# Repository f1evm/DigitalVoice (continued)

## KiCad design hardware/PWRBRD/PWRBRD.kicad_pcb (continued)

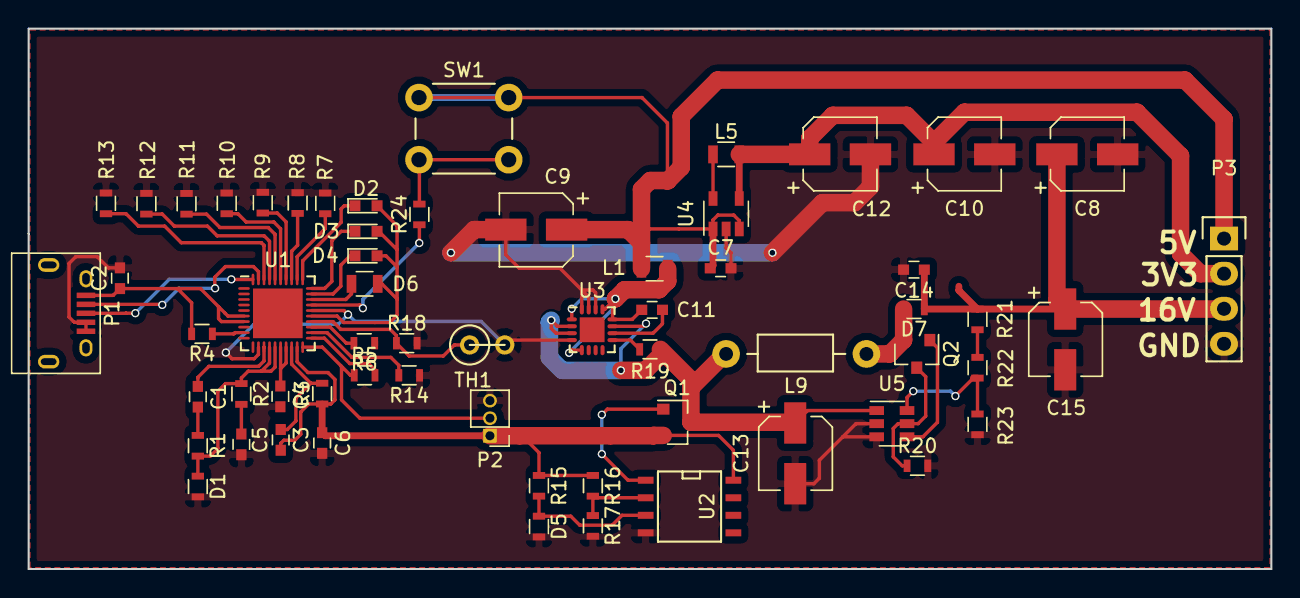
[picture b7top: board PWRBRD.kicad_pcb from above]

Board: 2 copper layers, 90.0 x 39.1 mm, 61 parts (0 on the bottom side), 47 nets.

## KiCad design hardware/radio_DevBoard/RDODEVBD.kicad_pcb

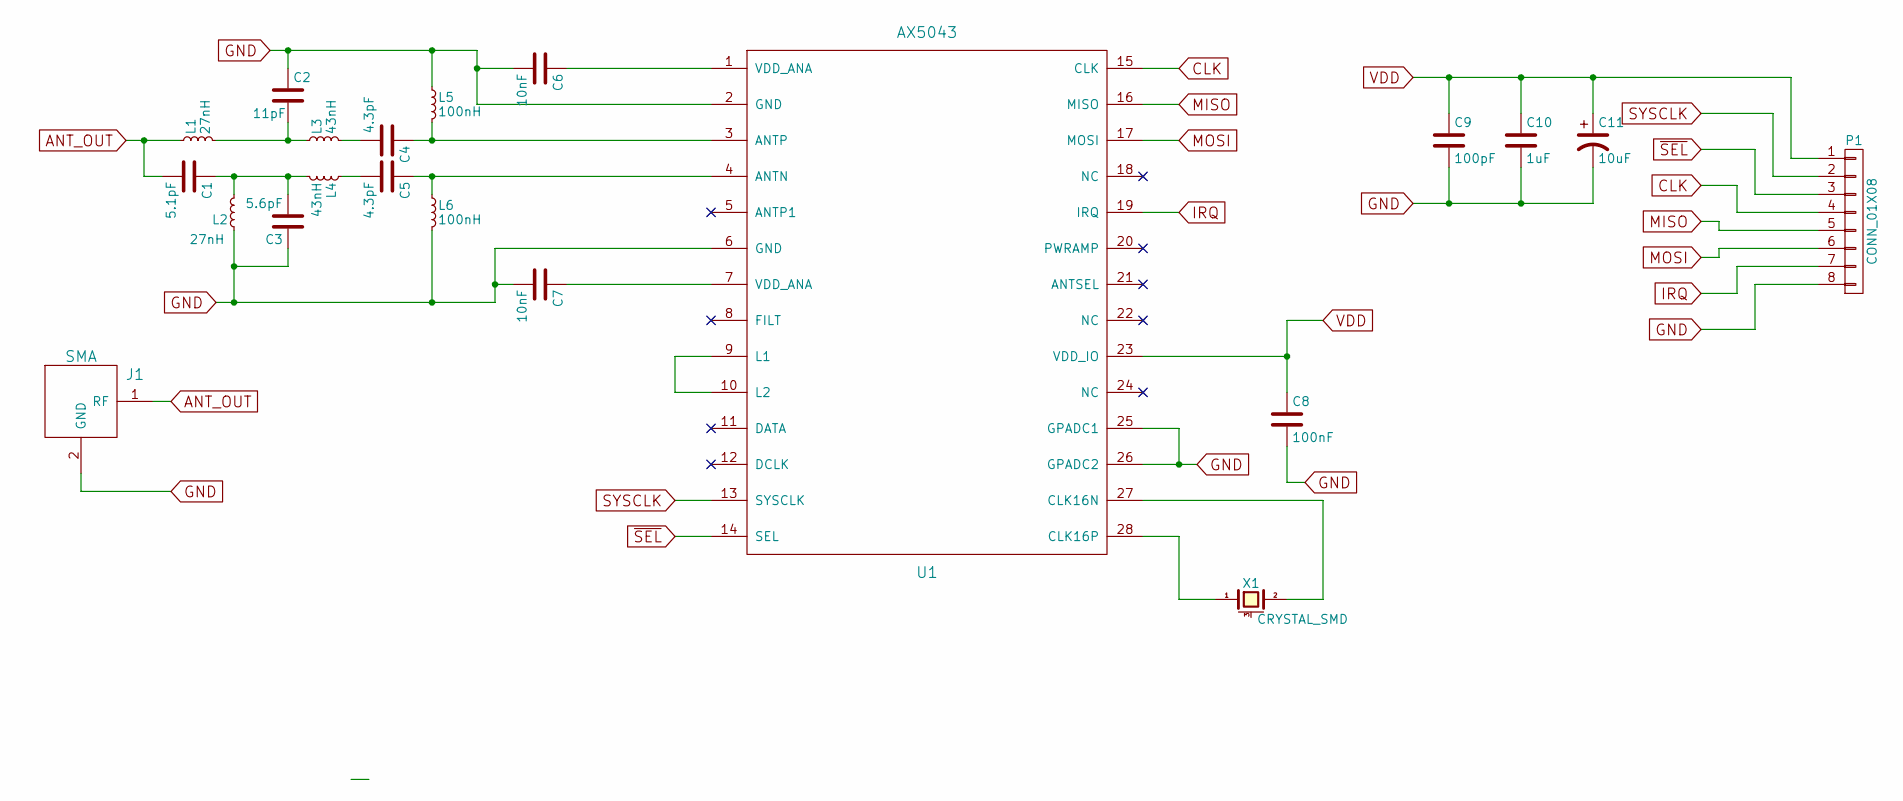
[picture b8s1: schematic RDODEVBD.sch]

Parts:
C1: 5.1pF; C_0805
C2: 11pF; C_0805
C3: 5.6pF; C_0805
C4, C5: 4.3pF; C_0805
C6, C7: 10nF; C_0805
C8: 100nF; C_0805
C9: 100pF; C_0805
C10: 1uF; C_0805
C11: 10uF; c_elec_5x5.3
J1: SMA; SMACONN
L1, L2: 27nH; R_0603
L3, L4: 43nH; R_0603
L5, L6: 100nH; R_0603
P1: CONN_01X08; Pin_Header_Straight_1x08
U1: AX5043; QFN-28-1EP_5x5mm_Pitch0.5mm
X1: CRYSTAL_SMD; Crystal_SMD_5032_4Pads

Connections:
ANT_OUT: C1.2, J1.1 (RF), L1.1
CLK: P1.4, U1.15 (CLK)
GND: C2.1, C3.1, C6.2, C7.2, C8.2, C9.2, C10.2, C11.2, J1.2 (GND), L2.1, L5.1, L6.2, P1.8, U1.2 (GND), U1.6 (GND), U1.25 (GPADC1), U1.26 (GPADC2)
IRQ: P1.7, U1.19 (IRQ)
MISO: P1.5, U1.16 (MISO)
MOSI: P1.6, U1.17 (MOSI)
unnamed: C1.1, C3.2, L2.2, L4.2
unnamed: C2.2, L1.2, L3.1
unnamed: C4.1, L5.2, U1.3 (ANTP)
unnamed: C4.2, L3.2
unnamed: C5.1, L6.1, U1.4 (ANTN)
unnamed: C5.2, L4.1
unnamed: C6.1, U1.1 (VDD_ANA)
unnamed: C7.1, U1.7 (VDD_ANA)
unnamed: U1.9 (L1), U1.10 (L2)
unnamed: U1.27 (CLK16N), X1.2
unnamed: U1.28 (CLK16P), X1.1
SYSCLK: P1.2, U1.13 (SYSCLK)
VDD: C8.1, C9.1, C10.1, C11.1, P1.1, U1.23 (VDD_IO)
~SEL: P1.3, U1.14 (SEL)

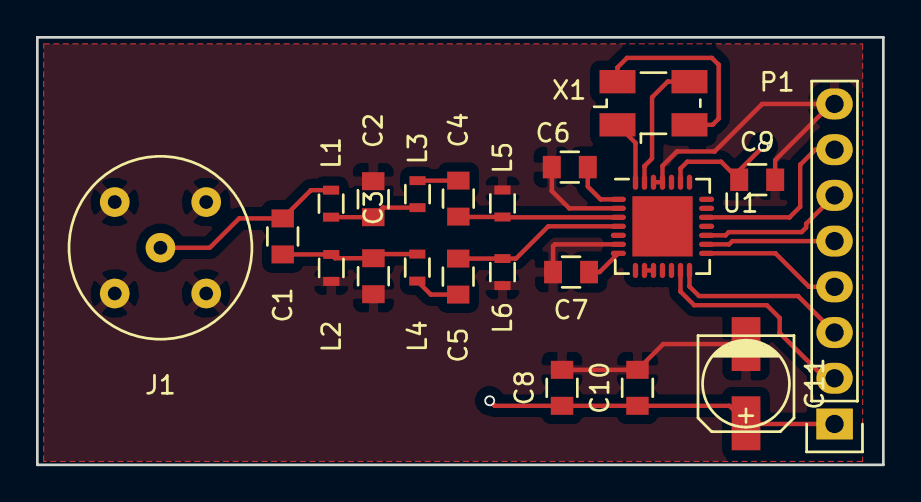
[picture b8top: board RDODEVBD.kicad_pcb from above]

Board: 4 copper layers, 47.0 x 23.8 mm, 21 parts (0 on the bottom side), 20 nets.

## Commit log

2017-01-20 Added Radio Developmental Board KiCAD files.
2017-02-03 Finished Radio Interface Dev & Audio Dev Schematic
2017-02-10 Added Battery Charger
    Added MCP73833 to Schematic
2017-02-15 Added Audio Card
    Added MP45T02 to schematic
2017-02-17 Create PlatformIO framework for software
2017-02-18 Build framework for AX5043 driver
2017-02-19 Added whole chain & Beginning of Power. Has a 7V charger and low voltage lockout.
2017-02-22 Added 3V3, 5V, and 16V switching.
2017-02-22 Should now ACTUALLY include power distribution schematic.
2017-02-22 Updated the Layout for the BMS portion.
2017-02-27 Finished laying out and prettifying the BMS/Distribution Board.
2017-02-28 Switch to EmBitz for debugger support
2017-02-28 Add Codec2 sources
2017-03-02 SM1000 compiles under EmBitz ... somehow
2017-03-04 Removed some excessive Inductances.
2017-03-09 Fix: gitignore would incorrectly flag KiCAD libraries as build artifacts
2017-03-10 C driver framework for pi
2017-03-10 Add LCD test script for pi zero
2017-03-10 Added bits of the RF Board, dumped to PCB.
2017-03-11 Stuff
2017-03-12 Add simple test to make sure SPI is set up right
2017-03-12 Register test builds
2017-03-12 Added some Amplification Chain work.
2017-03-12 Add Ax5043 radioLab project for configuration. Will not be in final release, but helps debugging
2017-03-12 First stab at fifo based transmit
2017-03-12 Builds, but still doesn't transmit
2017-03-19 Added some via stitching to start with.
2017-03-19 Added a little more.
2017-03-19 Added Internals of Board.
2017-03-22 Added an Si4464 Demo.
2017-03-22 Added further progress to Si4464 Radio Dev Board.
2017-03-27 Cleanup and Pihat.
2017-03-30 Added Libraries - Unzip.
2017-04-02 Fix ignored KiCad libraries
2017-04-02 Added PiHat updates.
2017-04-02 More updates, improvements, pihat.
2017-04-02 Butterworth Filter design
    Have a couple tweeks to make but nearly finished
2017-04-02 Added a bit more to the routing.
2017-04-04 New pihat for Pi3.
2017-04-04 Added some Silkscreen.
2017-04-05 Finished Silkscreen Work.
2017-04-07 Prepared new Board.
2017-04-07 tweaks for better pcb
2017-04-08 Began work on RX/TX schematic.
2017-04-12 Added more to the Schematic.
2017-04-14 Add RadioHead packet library. Not yet ported to WiringPi
2017-04-14 Began Layout, Pihat final.
2017-04-14 Pot footprint
2017-04-14 PCB Layout Changes
    minor changes, will continue layout
2017-04-14 Port interrupts and genericSpi from BCM2835 to WiringPi. Doesn't compile yet
2017-04-14 Turns out it was a makefile issue
2017-04-21 Pihat PCB Changes
    layout
2017-04-21 Pihat Update Again
2017-04-22 Worked on RF Layout.
2017-04-22 Transciever wiring & Power Distribution Changes, modified footprint for Edge SMA, swapped TX/RX on ANTSEL
2017-04-22 Reworked some power wiring, pausing to explore options regarding power routing.
2017-04-26 Minor changes to pihat 2 in prep for boardhouse #2.
2017-04-26 Re-Established Vias.
2017-04-26 Re-Routed a power trace to provide unbroken ground plane.
2017-04-26 Changed 5V Trace Size
2017-04-26 Fixed issues with grounding and trace size.
2017-04-27 Fixed some Schematic update changes that KiCAD pushed on us.
2017-04-27 Fixed via sizes.
2017-05-04 Add pin mapping
2017-05-05 Add channel simulation
